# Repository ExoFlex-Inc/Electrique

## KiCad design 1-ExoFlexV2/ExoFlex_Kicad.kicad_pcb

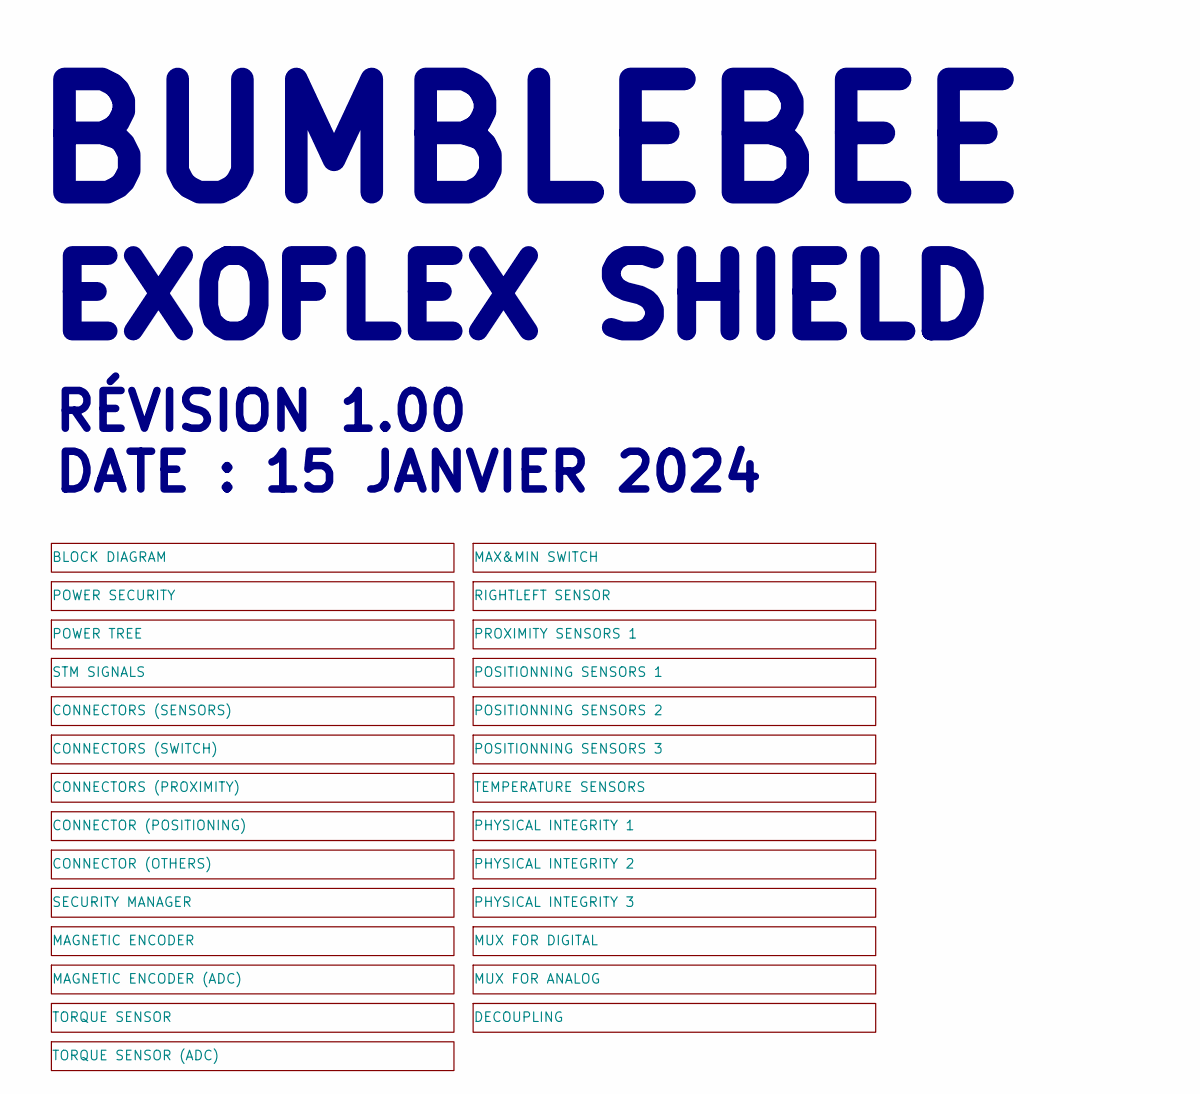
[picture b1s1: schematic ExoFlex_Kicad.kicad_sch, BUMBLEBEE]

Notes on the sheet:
BUMBLEBEE
EXOFLEX SHIELD
RÉVISION 1.00 DATE : 15 JANVIER 2024

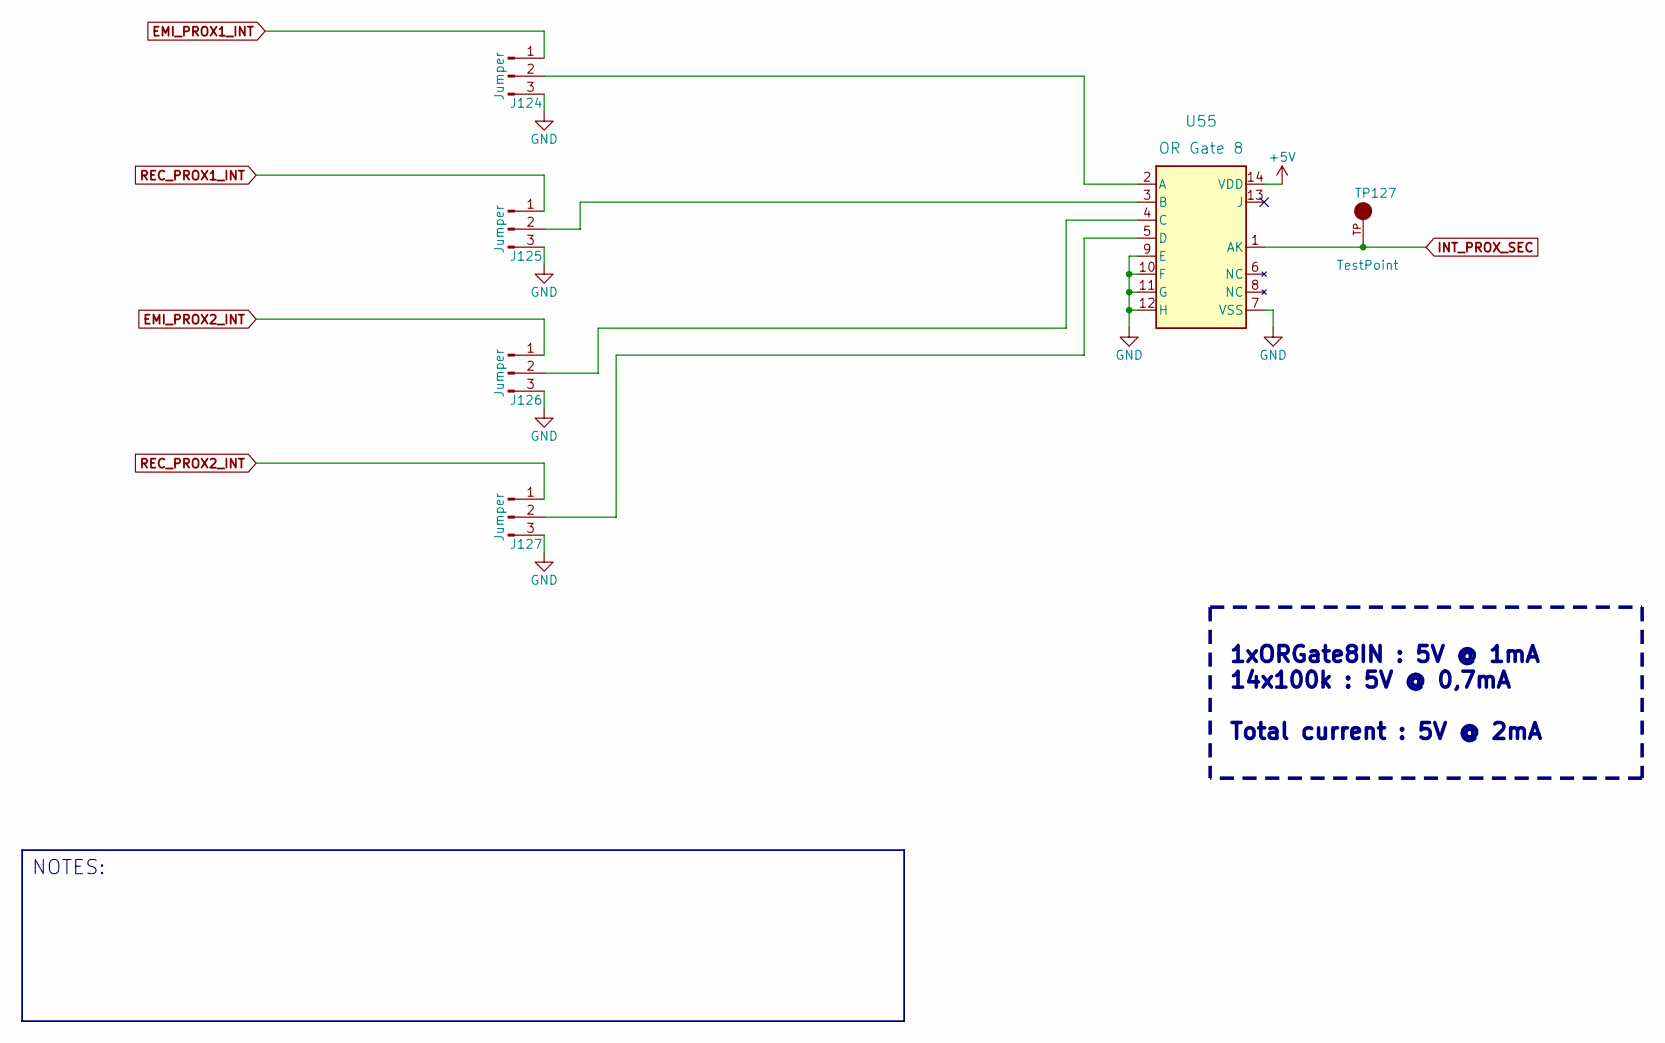
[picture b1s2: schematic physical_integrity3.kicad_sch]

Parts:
J124, J125, J126, J127: Jumper; PinHeader_1x03_P2.54mm_Vertical; PART NUMBER 61300311121
TP127: TestPoint; KEYSTONE_5005; PART NUMBER 5005
U55: OR Gate 8; D14; PART NUMBER CD4078BM96

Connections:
+5V: U55.14 (VDD); also elsewhere on the board
EMI_PROX1_INT: J124.1; also elsewhere on the board
EMI_PROX2_INT: J126.1; also elsewhere on the board
GND: J124.3, J125.3, J126.3, J127.3, U55.7 (VSS), U55.9 (E), U55.10 (F), U55.11 (G), U55.12 (H); also elsewhere on the board
INT_PROX_SEC: TP127.TP, U55.1 (AK); also elsewhere on the board
unnamed: J124.2, U55.2 (A)
unnamed: J125.2, U55.3 (B)
unnamed: J126.2, U55.4 (C)
unnamed: J127.2, U55.5 (D)
REC_PROX1_INT: J125.1; also elsewhere on the board
REC_PROX2_INT: J127.1; also elsewhere on the board

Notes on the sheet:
1xORGate8IN : 5V @ 1mA 14x100k : 5V @ 0,7mA Total current : 5V @ 2mA
NOTES:

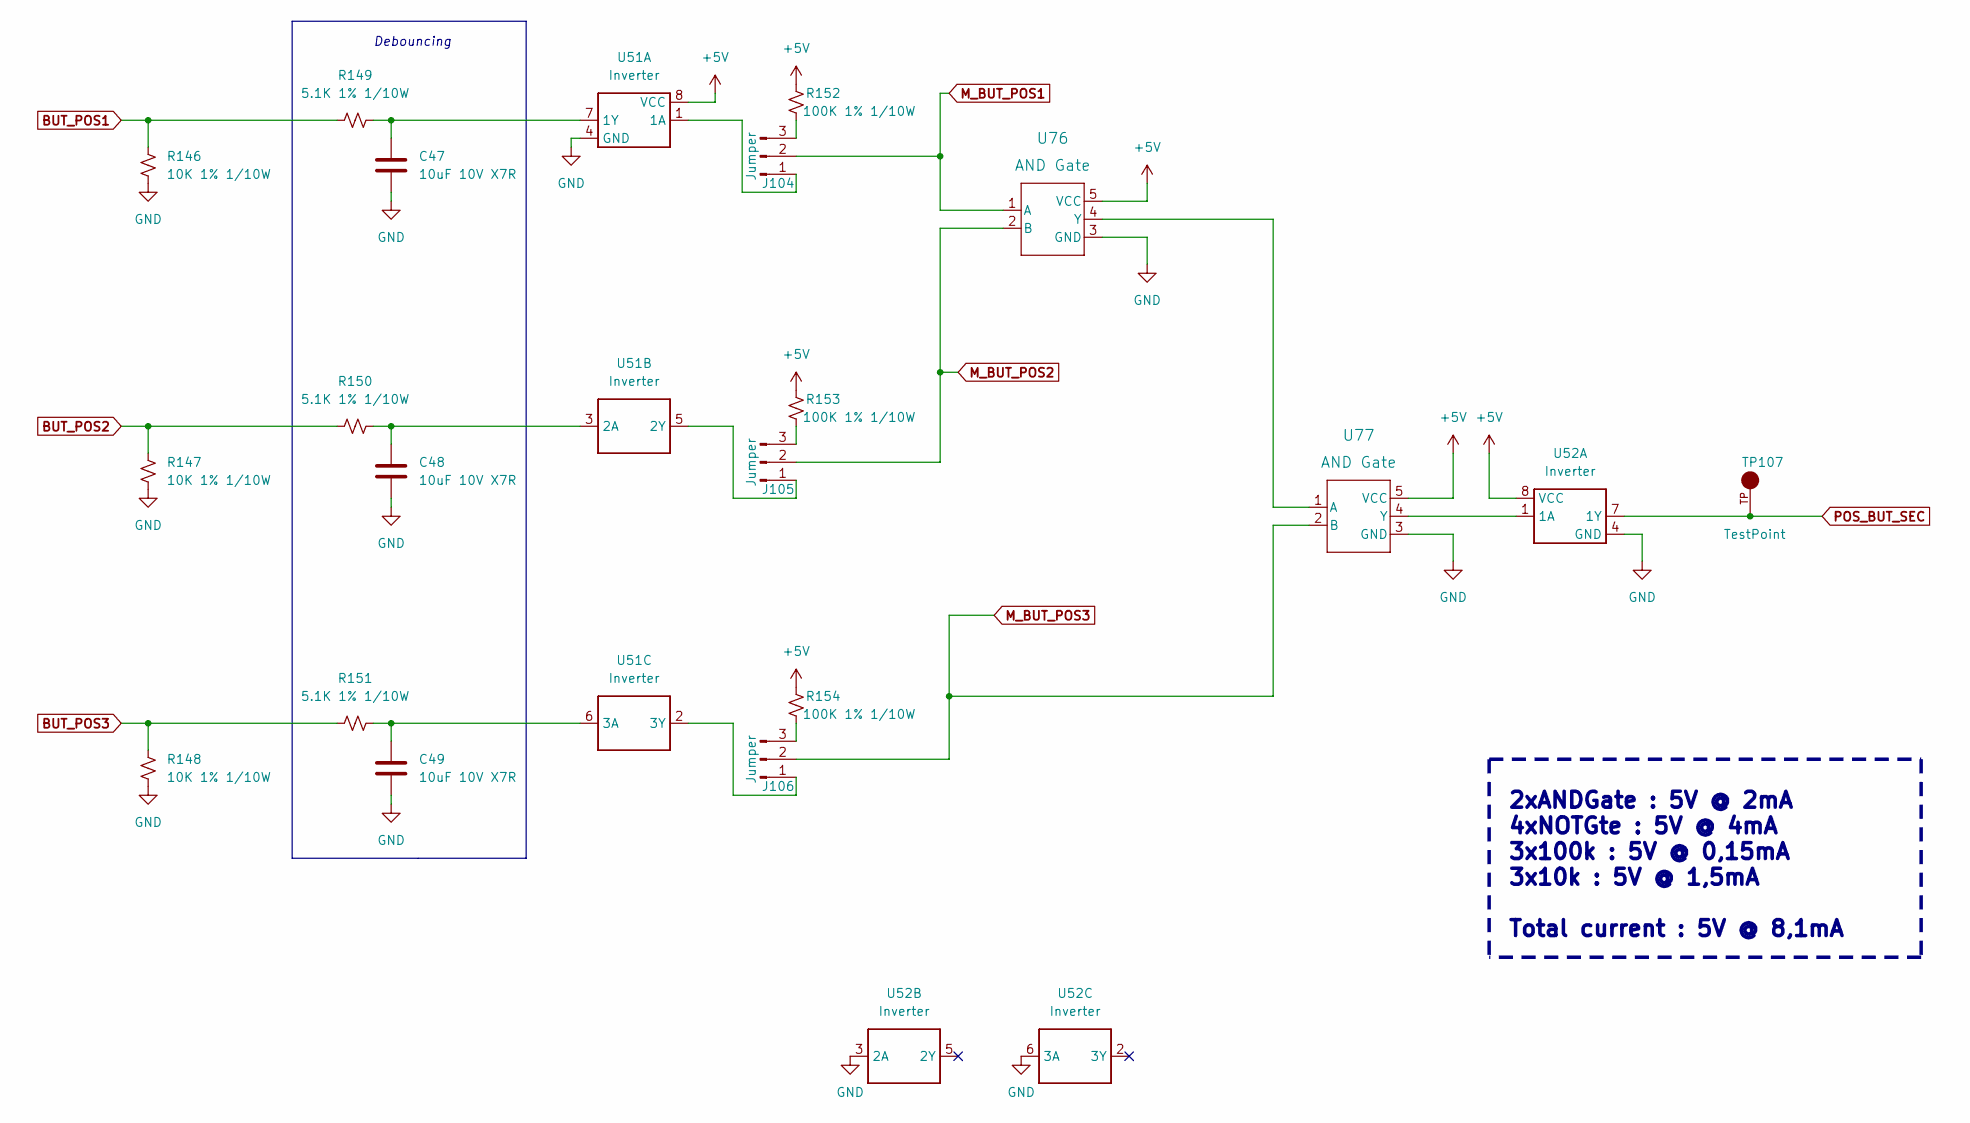
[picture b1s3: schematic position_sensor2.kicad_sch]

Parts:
C47, C48, C49: 10uF 10V X7R; C_0805_2012Metric; PART NUMBER GRM21BR71A106KA73L
J104, J105, J106: Jumper; PinHeader_1x03_P2.54mm_Vertical; PART NUMBER 61300311121
R146, R147, R148: 10K 1% 1/10W; R_0603_1608Metric; PART NUMBER ERJ-3EKF1002V
R149, R150, R151: 5.1K 1% 1/10W; R_0603_1608Metric; PART NUMBER ERJ-3EKF5101V
R152, R153, R154: 100K 1% 1/10W; R_0603_1608Metric; PART NUMBER ERJ-3EKF1003V
TP107: TestPoint; KEYSTONE_5005; PART NUMBER 5005
U51, U52: Inverter; SN74LVC3G14DCUT; PART NUMBER SN74LVC3G14DCUT
U76, U77: AND Gate; SOT95P270X145-5N; PART NUMBER SN74LVC1G08DBVR

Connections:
+5V: R152.2, R153.2, R154.2, U51.8 (VCC), U52.8 (VCC), U76.5 (VCC), U77.5 (VCC); also elsewhere on the board
BUT_POS1: R146.1, R149.1; also elsewhere on the board
BUT_POS2: R147.1, R150.1; also elsewhere on the board
BUT_POS3: R148.1, R151.1; also elsewhere on the board
GND: C47.2, C48.2, C49.2, R146.2, R147.2, R148.2, U51.4 (GND), U52.3 (2A), U52.4 (GND), U52.6 (3A), U76.3 (GND), U77.3 (GND); also elsewhere on the board
M_BUT_POS1: J104.2, U76.1 (A); also elsewhere on the board
M_BUT_POS2: J105.2, U76.2 (B); also elsewhere on the board
M_BUT_POS3: J106.2, U77.2 (B); also elsewhere on the board
unnamed: C47.1, R149.2, U51.7 (1Y)
unnamed: C48.1, R150.2, U51.3 (2A)
unnamed: C49.1, R151.2, U51.6 (3A)
unnamed: J104.1, U51.1 (1A)
unnamed: J104.3, R152.1
unnamed: J105.1, U51.5 (2Y)
unnamed: J105.3, R153.1
unnamed: J106.1, U51.2 (3Y)
unnamed: J106.3, R154.1
unnamed: U52.1 (1A), U77.4 (Y)
unnamed: U76.4 (Y), U77.1 (A)
POS_BUT_SEC: TP107.TP, U52.7 (1Y); also elsewhere on the board

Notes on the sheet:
2xANDGate : 5V @ 2mA 4xNOTGte : 5V @ 4mA 3x100k : 5V @ 0,15mA 3x10k : 5V @ 1,5mA Total current : 5V @ 8,1mA
Debouncing

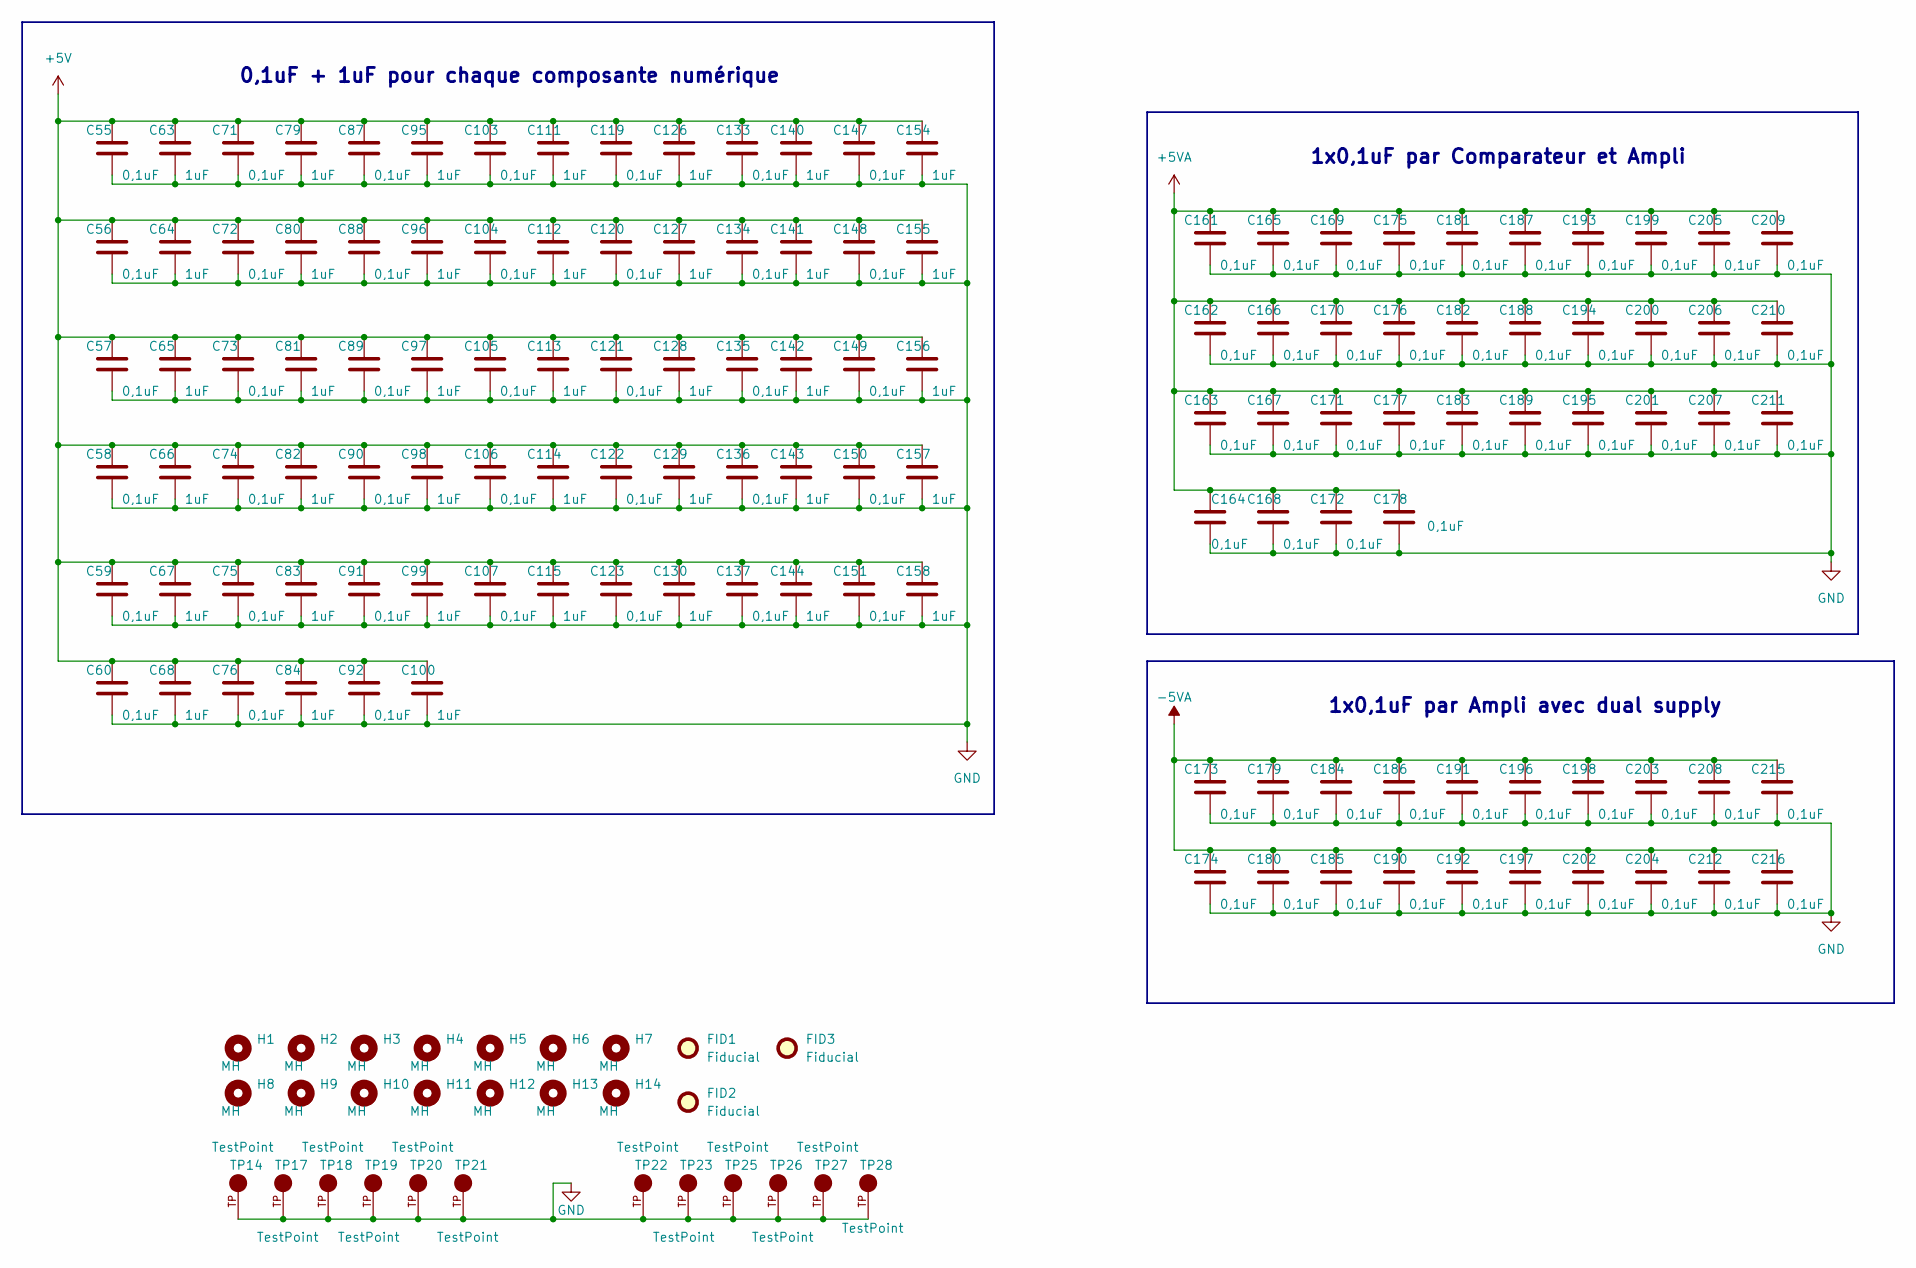
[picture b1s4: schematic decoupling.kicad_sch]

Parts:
C55, C56, C57, C58, C59, C60, C71, C72, C73, C74, C75, C76, C87, C88, C89, C90, C91, C92, C103, C104, C105, C106, C107, C119, C120, C121, C122, C123, C133, C134, C135, C136, C137, C147, C148, C149, C150, C151, C161, C162, C163, C164, C165, C166, C167, C168, C169, C170, C171, C172, C173, C174, C175, C176, C177, C178, C179, C180, C181, C182, C183, C184, C185, C186, C187, C188, C189, C190, C191, C192, C193, C194, C195, C196, C197, C198, C199, C200, C201, C202, C203, C204, C205, C206, C207, C208, C209, C210, C211, C212, C215, C216: 0,1uF; C_0402_1005Metric; PART NUMBER GRM155R61A104KA01D
C63, C64, C65, C66, C67, C68, C79, C80, C81, C82, C83, C84, C95, C96, C97, C98, C99, C100, C111, C112, C113, C114, C115, C126, C127, C128, C129, C130, C140, C141, C142, C143, C144, C154, C155, C156, C157, C158: 1uF; C_0402_1005Metric; PART NUMBER GRM155C81A105KA12D
FID1, FID2, FID3: Fiducial; Fiducial_0.5mm_Mask1.5mm
H1, H2, H3, H4, H5, H6, H7, H8, H9, H10, H11, H12, H13, H14: MH; MountingHole_2.2mm_M2
TP14, TP17, TP18, TP19, TP20, TP21, TP22, TP23, TP25, TP26, TP27, TP28: TestPoint; KEYSTONE_5005; PART NUMBER 5005

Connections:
+5V: C55.1, C56.1, C57.1, C58.1, C59.1, C60.1, C63.1, C64.1, C65.1, C66.1, C67.1, C68.1, C71.1, C72.1, C73.1, C74.1, C75.1, C76.1, C79.1, C80.1, C81.1, C82.1, C83.1, C84.1, C87.1, C88.1, C89.1, C90.1, C91.1, C92.1, C95.1, C96.1, C97.1, C98.1, C99.1, C100.1, C103.1, C104.1, C105.1, C106.1, C107.1, C111.1, C112.1, C113.1, C114.1, C115.1, C119.1, C120.1, C121.1, C122.1, C123.1, C126.1, C127.1, C128.1, C129.1, C130.1, C133.1, C134.1, C135.1, C136.1, C137.1, C140.1, C141.1, C142.1, C143.1, C144.1, C147.1, C148.1, C149.1, C150.1, C151.1, C154.1, C155.1, C156.1, C157.1, C158.1; also elsewhere on the board
+5VA: C161.1, C162.1, C163.1, C164.1, C165.1, C166.1, C167.1, C168.1, C169.1, C170.1, C171.1, C172.1, C175.1, C176.1, C177.1, C178.1, C181.1, C182.1, C183.1, C187.1, C188.1, C189.1, C193.1, C194.1, C195.1, C199.1, C200.1, C201.1, C205.1, C206.1, C207.1, C209.1, C210.1, C211.1; also elsewhere on the board
-5VA: C173.1, C174.1, C179.1, C180.1, C184.1, C185.1, C186.1, C190.1, C191.1, C192.1, C196.1, C197.1, C198.1, C202.1, C203.1, C204.1, C208.1, C212.1, C215.1, C216.1; also elsewhere on the board
GND: C55.2, C56.2, C57.2, C58.2, C59.2, C60.2, C63.2, C64.2, C65.2, C66.2, C67.2, C68.2, C71.2, C72.2, C73.2, C74.2, C75.2, C76.2, C79.2, C80.2, C81.2, C82.2, C83.2, C84.2, C87.2, C88.2, C89.2, C90.2, C91.2, C92.2, C95.2, C96.2, C97.2, C98.2, C99.2, C100.2, C103.2, C104.2, C105.2, C106.2, C107.2, C111.2, C112.2, C113.2, C114.2, C115.2, C119.2, C120.2, C121.2, C122.2, C123.2, C126.2, C127.2, C128.2, C129.2, C130.2, C133.2, C134.2, C135.2, C136.2, C137.2, C140.2, C141.2, C142.2, C143.2, C144.2, C147.2, C148.2, C149.2, C150.2, C151.2, C154.2, C155.2, C156.2, C157.2, C158.2, C161.2, C162.2, C163.2, C164.2, C165.2, C166.2, C167.2, C168.2, C169.2, C170.2, C171.2, C172.2, C173.2, C174.2, C175.2, C176.2, C177.2, C178.2, C179.2, C180.2, C181.2, C182.2, C183.2, C184.2, C185.2, C186.2, C187.2, C188.2, C189.2, C190.2, C191.2, C192.2, C193.2, C194.2, C195.2, C196.2, C197.2, C198.2, C199.2, C200.2, C201.2, C202.2, C203.2, C204.2, C205.2, C206.2, C207.2, C208.2, C209.2, C210.2, C211.2, C212.2, C215.2, C216.2, TP14.TP, TP17.TP, TP18.TP, TP19.TP, TP20.TP, TP21.TP, TP22.TP, TP23.TP, TP25.TP, TP26.TP, TP27.TP, TP28.TP; also elsewhere on the board

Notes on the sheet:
1x0,1uF par Comparateur et Ampli
0,1uF + 1uF pour chaque composante numérique
1x0,1uF par Ampli avec dual supply

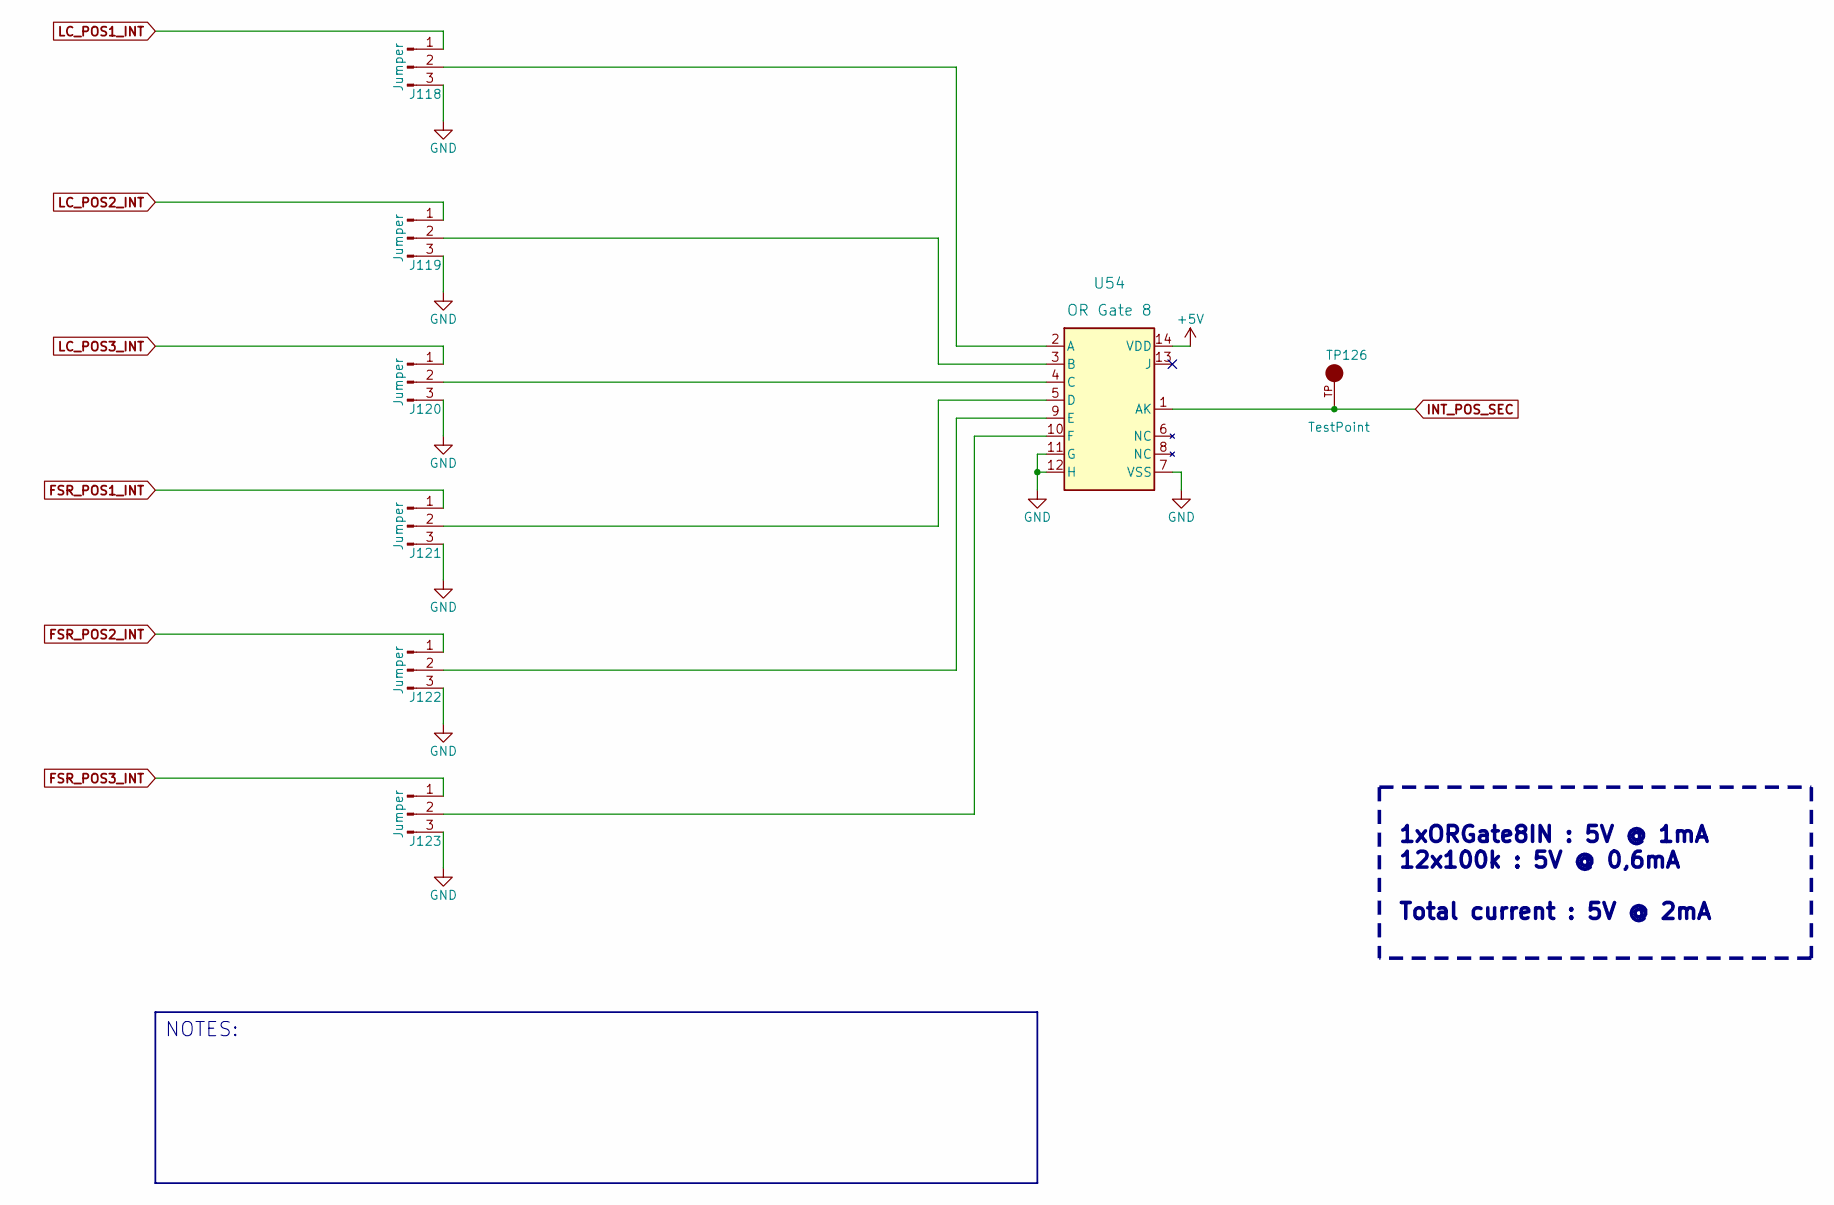
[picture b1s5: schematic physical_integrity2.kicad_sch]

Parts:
J118, J119, J120, J121, J122, J123: Jumper; PinHeader_1x03_P2.54mm_Vertical; PART NUMBER 61300311121
TP126: TestPoint; KEYSTONE_5005; PART NUMBER 5005
U54: OR Gate 8; D14; PART NUMBER CD4078BM96

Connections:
+5V: U54.14 (VDD); also elsewhere on the board
FSR_POS1_INT: J121.1; also elsewhere on the board
FSR_POS2_INT: J122.1; also elsewhere on the board
FSR_POS3_INT: J123.1; also elsewhere on the board
GND: J118.3, J119.3, J120.3, J121.3, J122.3, J123.3, U54.7 (VSS), U54.11 (G), U54.12 (H); also elsewhere on the board
INT_POS_SEC: TP126.TP, U54.1 (AK); also elsewhere on the board
LC_POS1_INT: J118.1; also elsewhere on the board
LC_POS2_INT: J119.1; also elsewhere on the board
LC_POS3_INT: J120.1; also elsewhere on the board
unnamed: J118.2, U54.2 (A)
unnamed: J119.2, U54.3 (B)
unnamed: J120.2, U54.4 (C)
unnamed: J121.2, U54.5 (D)
unnamed: J122.2, U54.9 (E)
unnamed: J123.2, U54.10 (F)

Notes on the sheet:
1xORGate8IN : 5V @ 1mA 12x100k : 5V @ 0,6mA Total current : 5V @ 2mA
NOTES:

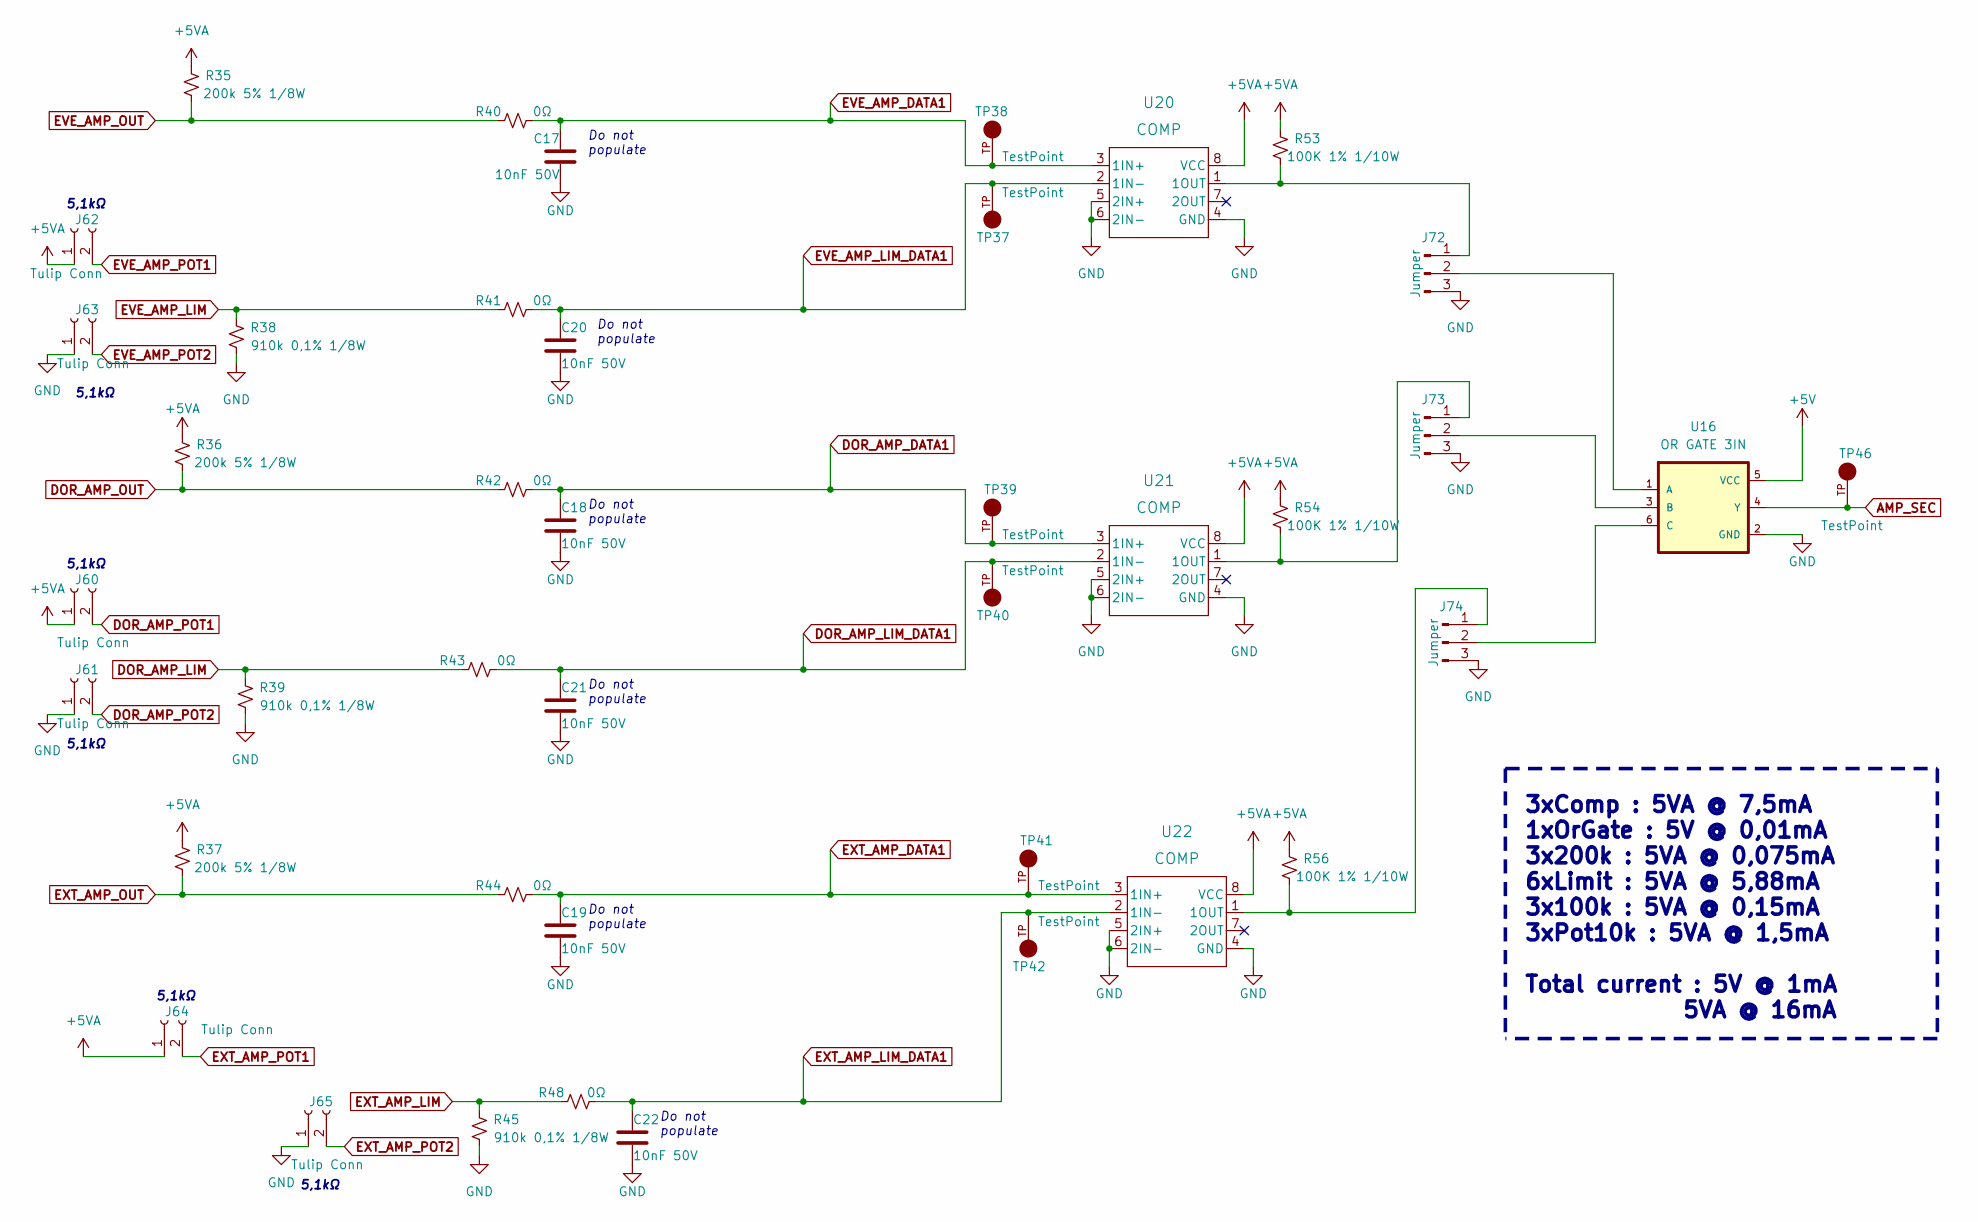
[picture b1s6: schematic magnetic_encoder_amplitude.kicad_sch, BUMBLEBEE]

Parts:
C17, C18, C19, C20, C21, C22: 10nF 50V; C_0805_2012Metric; PART NUMBER GRM2195C1H103JA01D
J60, J61, J62, J63, J64, J65: Tulip Conn; PinSocket_1x02_P2.54mm_Vertical; PART NUMBER 801-87-002-10-001101
J72, J73, J74: Jumper; PinHeader_1x03_P2.54mm_Vertical; PART NUMBER 61300311121
R35, R36, R37: 200k 5% 1/8W; R_0805_2012Metric; PART NUMBER ERJ-6GEYJ204V
R38, R39, R45: 910k 0,1% 1/8W; R_0805_2012Metric; PART NUMBER ERA-6AEB914V
R40, R41, R42, R43, R44, R48: 0Ω; R_0805_2012Metric; PART NUMBER ERJ-6GEY0R00V
R53, R54, R56: 100K 1% 1/10W; R_0603_1608Metric; PART NUMBER ERJ-3EKF1003V
TP37, TP38, TP39, TP40, TP41, TP42, TP46: TestPoint; KEYSTONE_5005; PART NUMBER 5005
U16: OR GATE 3IN; SOT95P280X145-6N; PART NUMBER SN74LVC1G332DBVR
U20, U21, U22: COMP; DGK8; PART NUMBER LM393DGKR

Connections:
+5V: U16.5 (VCC); also elsewhere on the board
+5VA: J60.1, J62.1, J64.1, R35.1, R36.1, R37.1, R53.1, R54.1, R56.1, U20.8 (VCC), U21.8 (VCC), U22.8 (VCC); also elsewhere on the board
AMP_SEC: TP46.TP, U16.4 (Y); also elsewhere on the board
DOR_AMP_DATA1: C18.1, R42.2, TP39.TP, U21.3 (1IN+); also elsewhere on the board
DOR_AMP_LIM: R39.1, R43.1; also elsewhere on the board
DOR_AMP_LIM_DATA1: C21.1, R43.2, TP40.TP, U21.2 (1IN-); also elsewhere on the board
DOR_AMP_OUT: R36.2, R42.1; also elsewhere on the board
DOR_AMP_POT1: J60.2; also elsewhere on the board
DOR_AMP_POT2: J61.2; also elsewhere on the board
EVE_AMP_DATA1: C17.1, R40.2, TP38.TP, U20.3 (1IN+); also elsewhere on the board
EVE_AMP_LIM: R38.1, R41.1; also elsewhere on the board
EVE_AMP_LIM_DATA1: C20.1, R41.2, TP37.TP, U20.2 (1IN-); also elsewhere on the board
EVE_AMP_OUT: R35.2, R40.1; also elsewhere on the board
EVE_AMP_POT1: J62.2; also elsewhere on the board
EVE_AMP_POT2: J63.2; also elsewhere on the board
EXT_AMP_DATA1: C19.1, R44.2, TP41.TP, U22.3 (1IN+); also elsewhere on the board
EXT_AMP_LIM: R45.1, R48.1; also elsewhere on the board
EXT_AMP_LIM_DATA1: C22.1, R48.2, TP42.TP, U22.2 (1IN-); also elsewhere on the board
EXT_AMP_OUT: R37.2, R44.1; also elsewhere on the board
EXT_AMP_POT1: J64.2; also elsewhere on the board
EXT_AMP_POT2: J65.2; also elsewhere on the board
GND: C17.2, C18.2, C19.2, C20.2, C21.2, C22.2, J61.1, J63.1, J65.1, J72.3, J73.3, J74.3, R38.2, R39.2, R45.2, U16.2 (GND), U20.4 (GND), U20.5 (2IN+), U20.6 (2IN-), U21.4 (GND), U21.5 (2IN+), U21.6 (2IN-), U22.4 (GND), U22.5 (2IN+), U22.6 (2IN-); also elsewhere on the board
unnamed: J72.1, R53.2, U20.1 (1OUT)
unnamed: J72.2, U16.1 (A)
unnamed: J73.1, R54.2, U21.1 (1OUT)
unnamed: J73.2, U16.3 (B)
unnamed: J74.1, R56.2, U22.1 (1OUT)
unnamed: J74.2, U16.6 (C)

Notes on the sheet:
Do not populate
5,1kΩ
3xComp : 5VA @ 7,5mA 1xOrGate : 5V @ 0,01mA 3x200k : 5VA @ 0,075mA 6xLimit : 5VA @ 5,88mA 3x100k : 5VA @ 0,15mA 3xPot10k : 5VA @ 1,5mA Total current : 5V @ 1mA 5VA @ 16mA

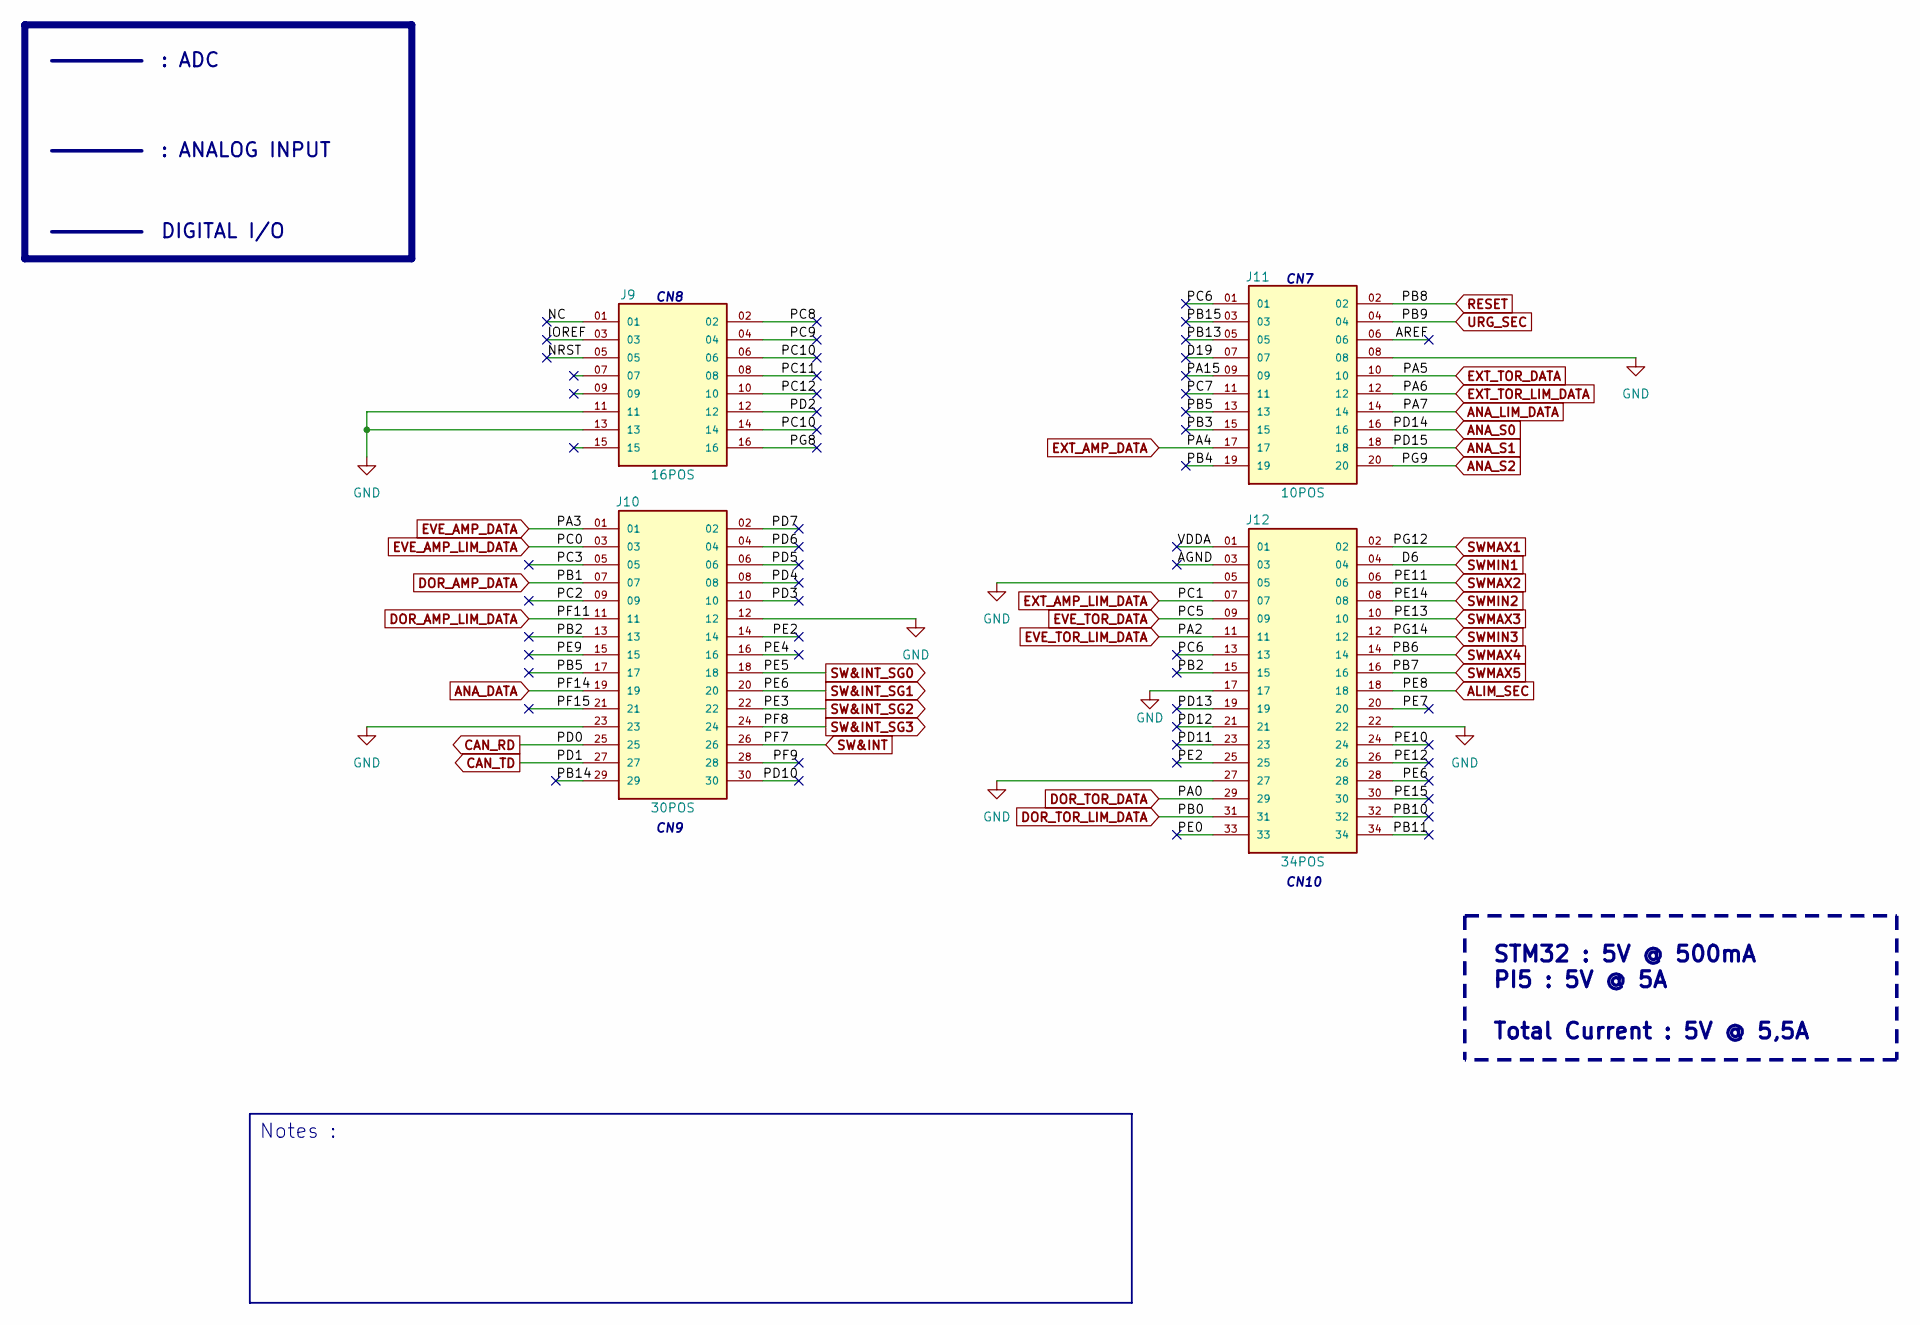
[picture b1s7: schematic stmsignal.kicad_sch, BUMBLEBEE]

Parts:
J9: 16POS; SAMTEC_SSW-108-01-G-D; PARTREV R
J10: 30POS; SAMTEC_SSW-115-01-G-D; PARTREV R
J11: 10POS; SAMTEC_SSW-110-01-G-D; PARTREV R
J12: 34POS; SAMTEC_SSW-117-01-G-D; PARTREV R

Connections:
/STM SIGNALS/AGND: J12.03
/STM SIGNALS/AREF: J11.06
/STM SIGNALS/D19: J11.07
/STM SIGNALS/IOREF: J9.03
/STM SIGNALS/NC: J9.01
/STM SIGNALS/NRST: J9.05
/STM SIGNALS/PA15: J11.09
/STM SIGNALS/PB2: J10.13, J12.15
/STM SIGNALS/PB3: J11.15
/STM SIGNALS/PB4: J11.19
/STM SIGNALS/PB5: J10.17, J11.13
/STM SIGNALS/PB10: J12.32
/STM SIGNALS/PB11: J12.34
/STM SIGNALS/PB13: J11.05
/STM SIGNALS/PB14: J10.29
/STM SIGNALS/PB15: J11.03
/STM SIGNALS/PC2: J10.09
/STM SIGNALS/PC3: J10.05
/STM SIGNALS/PC6: J11.01, J12.13
/STM SIGNALS/PC7: J11.11
/STM SIGNALS/PC8: J9.02
/STM SIGNALS/PC9: J9.04
/STM SIGNALS/PC10: J9.06, J9.14
/STM SIGNALS/PC11: J9.08
/STM SIGNALS/PC12: J9.10
/STM SIGNALS/PD2: J9.12
/STM SIGNALS/PD3: J10.10
/STM SIGNALS/PD4: J10.08
/STM SIGNALS/PD5: J10.06
/STM SIGNALS/PD6: J10.04
/STM SIGNALS/PD7: J10.02
/STM SIGNALS/PD10: J10.30
/STM SIGNALS/PD11: J12.23
/STM SIGNALS/PD12: J12.21
/STM SIGNALS/PD13: J12.19
/STM SIGNALS/PE0: J12.33
/STM SIGNALS/PE2: J10.14, J12.25
/STM SIGNALS/PE4: J10.16
/STM SIGNALS/PE7: J12.20
/STM SIGNALS/PE9: J10.15
/STM SIGNALS/PE10: J12.24
/STM SIGNALS/PE12: J12.26
/STM SIGNALS/PE15: J12.30
/STM SIGNALS/PF9: J10.28
/STM SIGNALS/PF15: J10.21
/STM SIGNALS/PG8: J9.16
/STM SIGNALS/VDDA: J12.01
ALIM_SEC: J12.18; also elsewhere on the board
ANA_DATA: J10.19; also elsewhere on the board
ANA_LIM_DATA: J11.14; also elsewhere on the board
ANA_S0: J11.16; also elsewhere on the board
ANA_S1: J11.18; also elsewhere on the board
ANA_S2: J11.20; also elsewhere on the board
CAN_RD: J10.25; also elsewhere on the board
CAN_TD: J10.27; also elsewhere on the board
DOR_AMP_DATA: J10.07; also elsewhere on the board
DOR_AMP_LIM_DATA: J10.11; also elsewhere on the board
DOR_TOR_DATA: J12.29; also elsewhere on the board
DOR_TOR_LIM_DATA: J12.31; also elsewhere on the board
EVE_AMP_DATA: J10.01; also elsewhere on the board
EVE_AMP_LIM_DATA: J10.03; also elsewhere on the board
EVE_TOR_DATA: J12.09; also elsewhere on the board
EVE_TOR_LIM_DATA: J12.11; also elsewhere on the board
EXT_AMP_DATA: J11.17; also elsewhere on the board
EXT_AMP_LIM_DATA: J12.07; also elsewhere on the board
EXT_TOR_DATA: J11.10; also elsewhere on the board
EXT_TOR_LIM_DATA: J11.12; also elsewhere on the board
GND: J9.11, J9.13, J10.12, J10.23, J11.08, J12.05, J12.17, J12.22, J12.27; also elsewhere on the board
RESET: J11.02; also elsewhere on the board
SW&INT: J10.26; also elsewhere on the board
SW&INT_SG0: J10.18; also elsewhere on the board
SW&INT_SG1: J10.20, J12.28; also elsewhere on the board
SW&INT_SG2: J10.22; also elsewhere on the board
SW&INT_SG3: J10.24; also elsewhere on the board
SWMAX1: J12.02; also elsewhere on the board
SWMAX2: J12.06; also elsewhere on the board
SWMAX3: J12.10; also elsewhere on the board
SWMAX4: J12.14; also elsewhere on the board
SWMAX5: J12.16; also elsewhere on the board
SWMIN1: J12.04; also elsewhere on the board
SWMIN2: J12.08; also elsewhere on the board
SWMIN3: J12.12; also elsewhere on the board
URG_SEC: J11.04; also elsewhere on the board

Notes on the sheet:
CN10
CN8
Notes :
STM32 : 5V @ 500mA PI5 : 5V @ 5A Total Current : 5V @ 5,5A
: ANALOG INPUT
CN9
DIGITAL I/O
CN7
: ADC
